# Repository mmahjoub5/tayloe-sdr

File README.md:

# tayloe-sdr
Custom Hardware &amp; SDR with ownership of entire stack

# credits
https://github.com/darius3241/Software-Defined-Radio

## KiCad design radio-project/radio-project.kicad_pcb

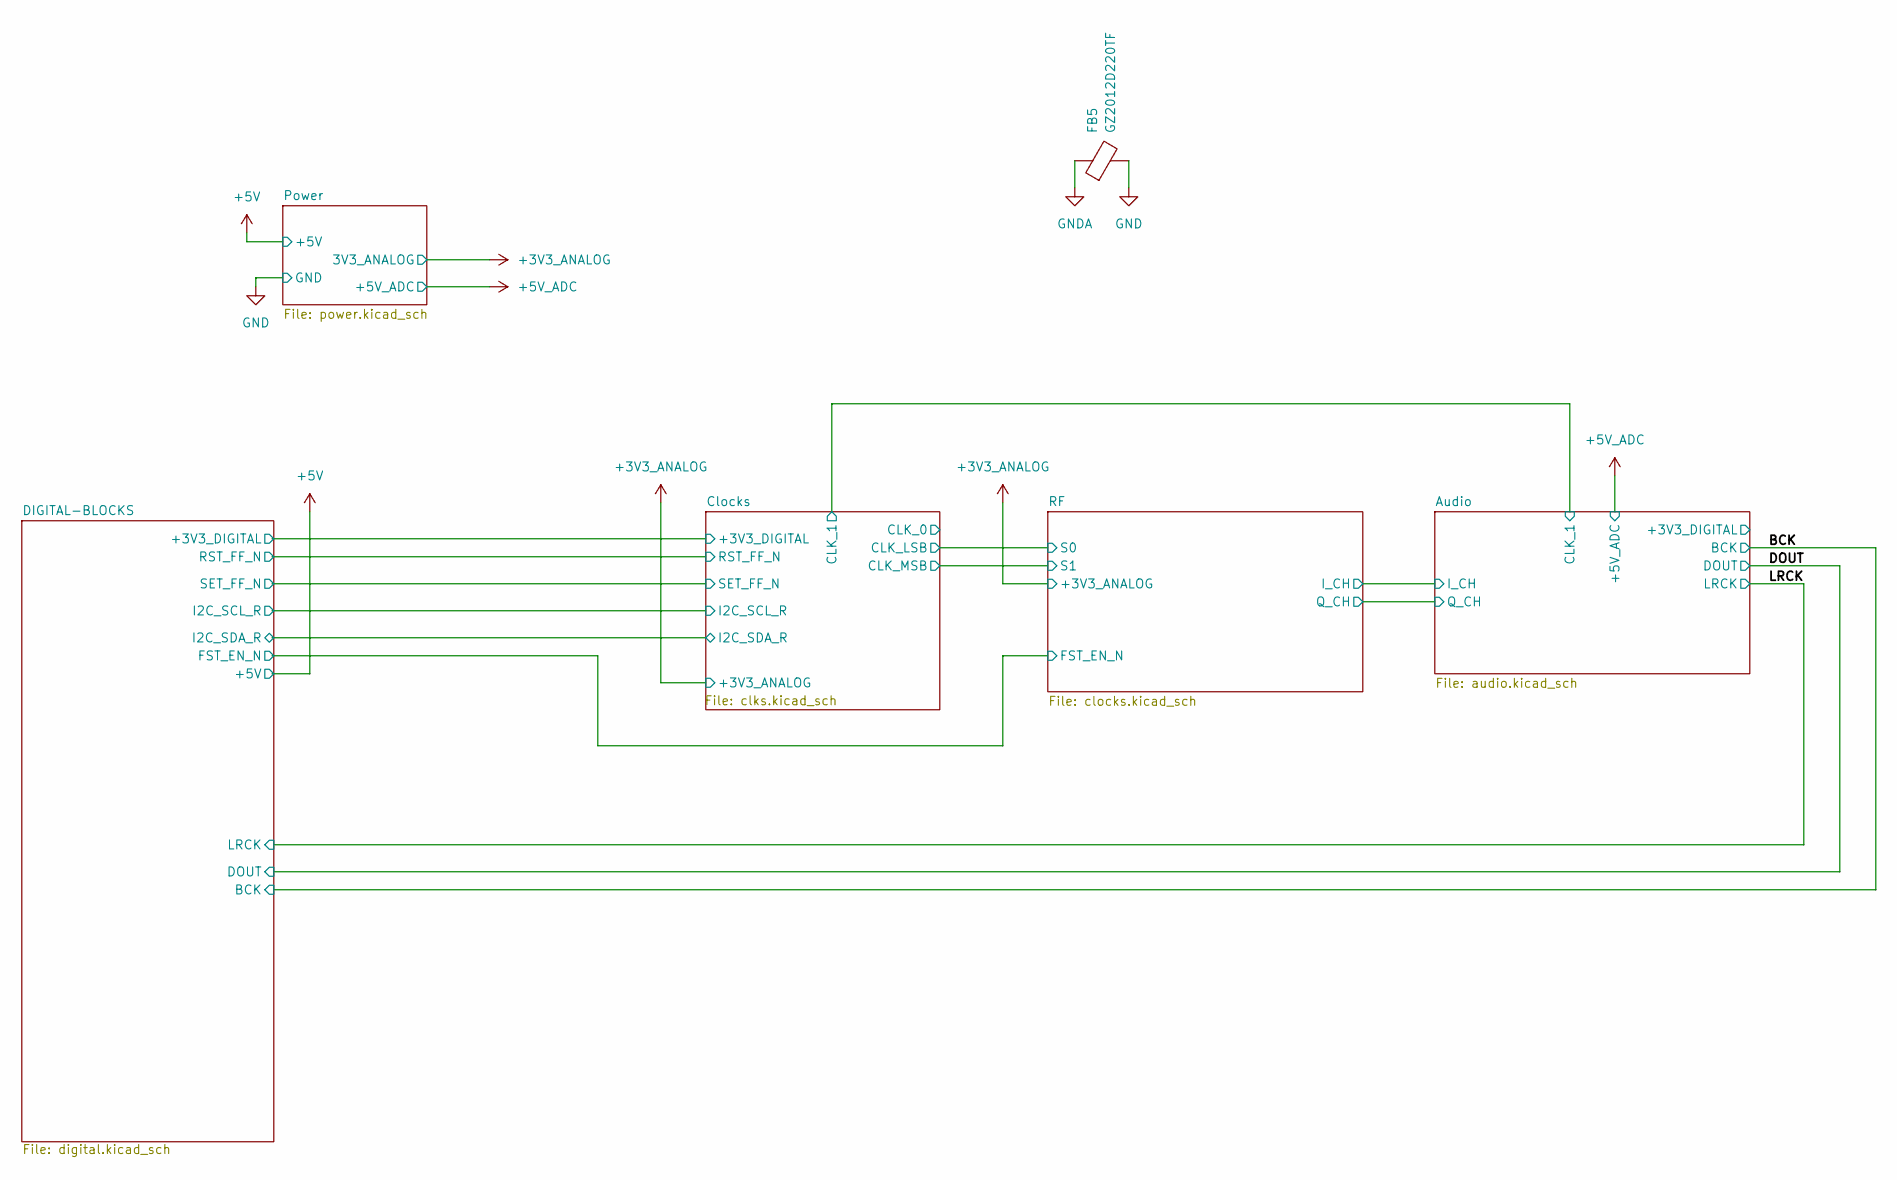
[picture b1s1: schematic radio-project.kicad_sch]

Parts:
FB5: GZ2012D220TF; L_0805_2012Metric

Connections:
GND: FB5.2; also elsewhere on the board
GNDA: FB5.1; also elsewhere on the board

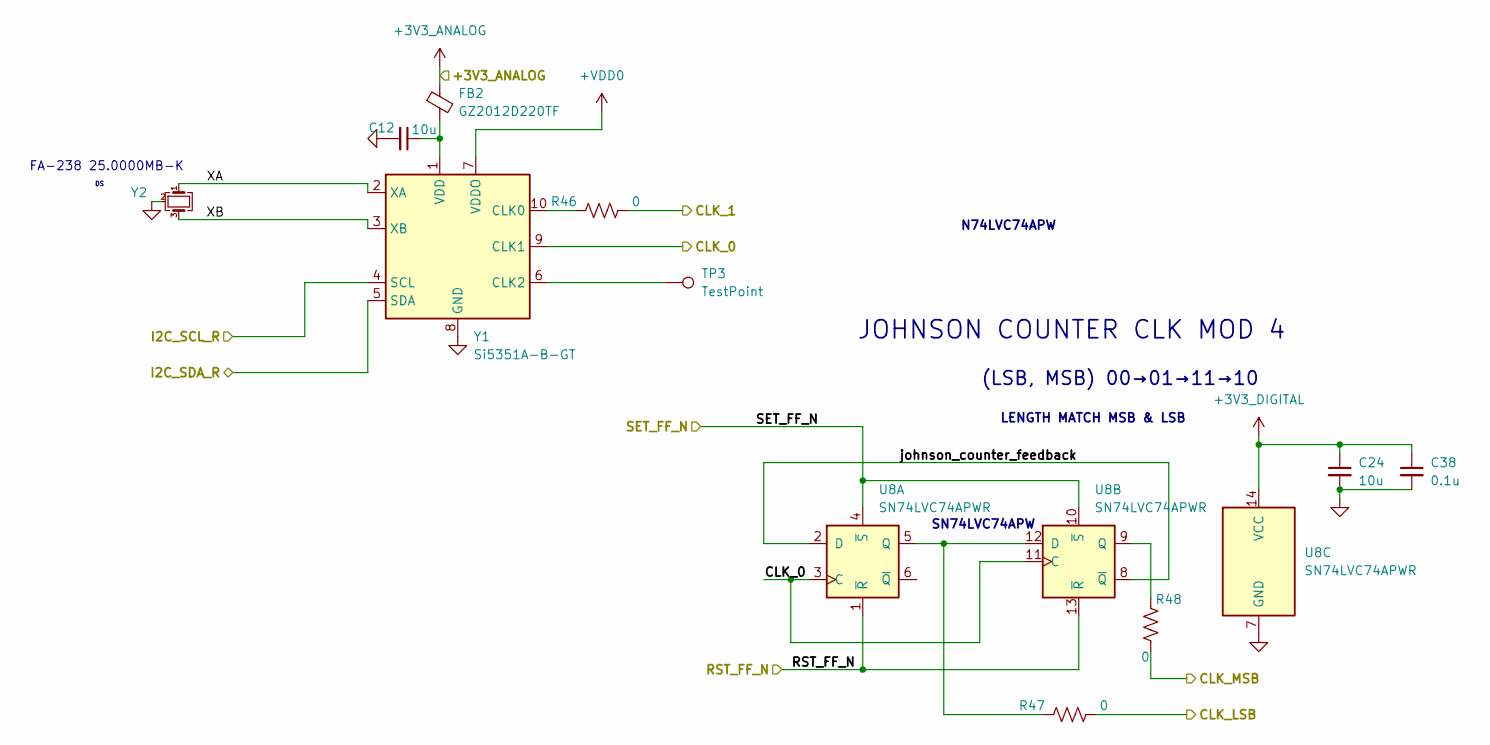
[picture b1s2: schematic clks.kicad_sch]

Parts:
C12, C24: 10u; C_0603_1608Metric
C38: 0.1u; C_0201_0603Metric
FB2: GZ2012D220TF; L_0805_2012Metric
R46, R47, R48: 0; R_0402_1005Metric
TP3: TestPoint; TestPoint_Pad_D1.0mm
U8: SN74LVC74APWR; TSSOP-14_4.4x5mm_P0.65mm
Y1: Si5351A-B-GT; MSOP-10_3x3mm_P0.5mm
Y2: 25Mhz; Crystal_SMD_3225-4Pin_3.2x2.5mm

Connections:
+3V3_ANALOG: FB2.1; also elsewhere on the board
+3V3_DIGITAL: C24.1, C38.1, U8.14 (VCC); also elsewhere on the board
+VDD0: Y1.7 (VDDO)
/Audio/CLK_1: R46.2; also elsewhere on the board
/Clocks/CLK_0: U8.3 (C), U8.11 (C), Y1.9 (CLK1)
/Clocks/CLK_LSB: R47.2; also elsewhere on the board
/Clocks/CLK_MSB: R48.2; also elsewhere on the board
/Clocks/I2C_SCL_R: Y1.4 (SCL); also elsewhere on the board
/Clocks/I2C_SDA_R: Y1.5 (SDA); also elsewhere on the board
/Clocks/RST_FF_N: U8.1 (~R), U8.13 (~R); also elsewhere on the board
/Clocks/SET_FF_N: U8.4 (~S), U8.10 (~S); also elsewhere on the board
/Clocks/XA: Y1.2 (XA), Y2.1
/Clocks/XB: Y1.3 (XB), Y2.3
/Clocks/johnson_counter_feedback: U8.2 (D), U8.8 (~Q)
GND: C12.2, C24.2, C38.2, U8.7 (GND), Y1.8 (GND), Y2.2 (G), Y2.4 (G); also elsewhere on the board
unnamed: R47.1, U8.5 (Q), U8.12 (D)
unnamed: R48.1, U8.9 (Q)
unnamed: R46.1, Y1.10 (CLK0)
unnamed: TP3.1 (1_1), Y1.6 (CLK2)
unnamed: C12.1, FB2.2, Y1.1 (VDD)

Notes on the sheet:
N74LVC74APW
JOHNSON COUNTER CLK MOD 4
FA-238 25.0000MB-K
SN74LVC74APW
(LSB, MSB) 00→01→11→10
LENGTH MATCH MSB & LSB

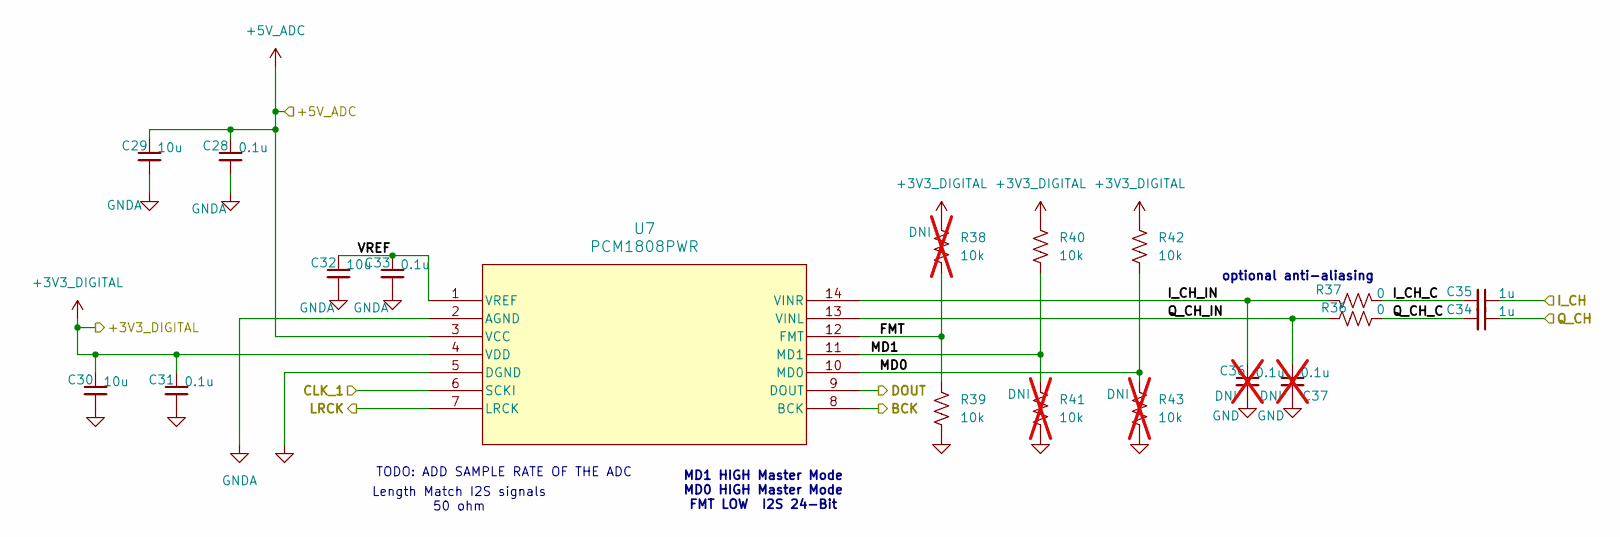
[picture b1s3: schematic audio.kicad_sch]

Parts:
C28, C31: 0.1u; C_0603_1608Metric
C29, C30, C32: 10u; C_0603_1608Metric
C33: 0.1u; C_0402_1005Metric
C34, C35: 1u; C_0402_1005Metric
C36, C37: 0.1u; C_0402_1005Metric; not fitted
R36, R37: 0; R_0402_1005Metric
R38, R41, R43: 10k; R_0402_1005Metric; not fitted
R39, R40, R42: 10k; R_0402_1005Metric
U7: PCM1808PWR; TSSOP-14_4.4x5mm_P0.65mm

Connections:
+3V3_DIGITAL: C30.1, C31.1, R38.1, R40.1, R42.1, U7.4 (VDD); also elsewhere on the board
+5V_ADC: C28.1, C29.1, U7.3 (VCC); also elsewhere on the board
/Audio/CLK_1: U7.6 (SCKI); also elsewhere on the board
/Audio/FMT: R38.2, R39.1, U7.12 (FMT)
/Audio/I_CH: C35.1; also elsewhere on the board
/Audio/I_CH_C: C35.2, R37.2
/Audio/I_CH_IN: C36.1, R37.1, U7.14 (VINR)
/Audio/MD0: R42.2, R43.1, U7.10 (MD0)
/Audio/MD1: R40.2, R41.1, U7.11 (MD1)
/Audio/Q_CH: C34.1; also elsewhere on the board
/Audio/Q_CH_C: C34.2, R36.2
/Audio/Q_CH_IN: C37.1, R36.1, U7.13 (VINL)
/Audio/VREF: C32.1, C33.1, U7.1 (VREF)
/BCK: U7.8 (BCK); also elsewhere on the board
/DOUT: U7.9 (DOUT); also elsewhere on the board
/LRCK: U7.7 (LRCK); also elsewhere on the board
GND: C30.2, C31.2, C36.2, C37.2, R39.2, R41.2, R43.2, U7.5 (DGND); also elsewhere on the board
GNDA: C28.2, C29.2, C32.2, C33.2, U7.2 (AGND); also elsewhere on the board

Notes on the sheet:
MD1 HIGH Master Mode MD0 HIGH Master Mode FMT LOW I2S 24-Bit
optional anti-aliasing
Length Match I2S signals 50 ohm
TODO: ADD SAMPLE RATE OF THE ADC

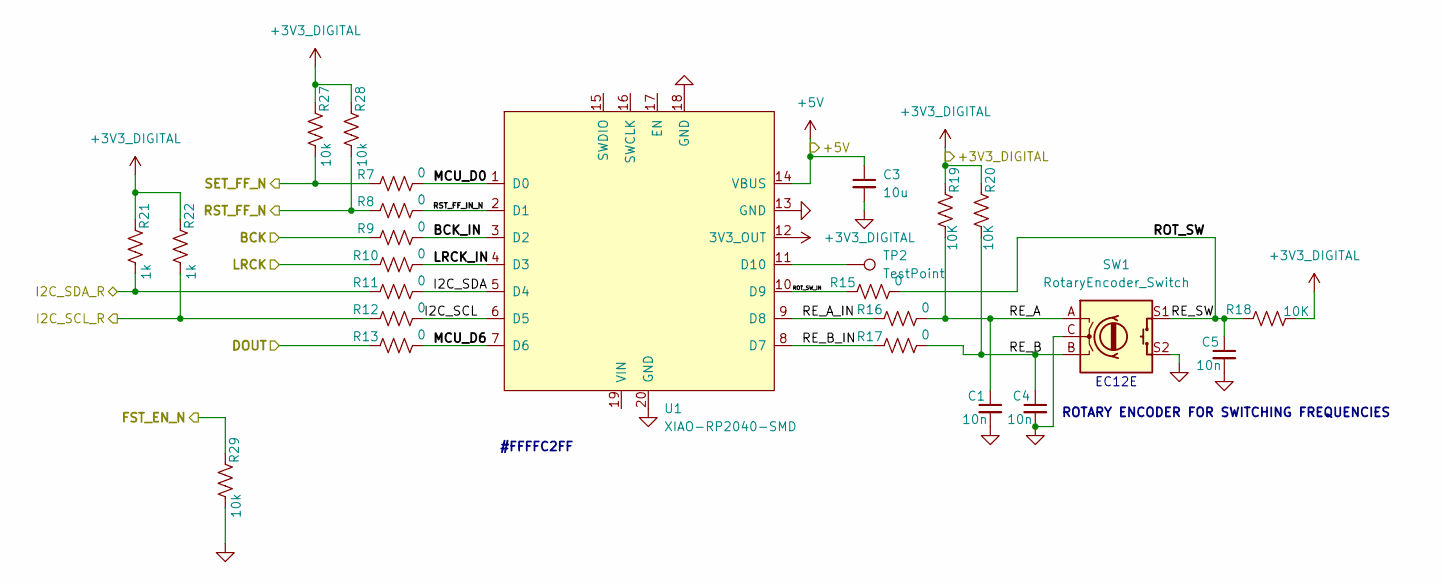
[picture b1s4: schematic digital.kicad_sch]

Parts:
C1, C4, C5: 10n; C_0402_1005Metric
C3: 10u; C_0603_1608Metric
R7, R8, R9, R10, R11, R12, R13, R15, R16, R17: 0; R_0402_1005Metric
R18, R19, R20: 10K; R_0402_1005Metric
R21, R22: 1k; R_0402_1005Metric
R27, R28, R29: 10k; R_0402_1005Metric
SW1: RotaryEncoder_Switch; RotaryEncoder_Alps_EC12E-Switch_Vertical_H20mm
TP2: TestPoint; TestPoint_Pad_D2.0mm
U1: XIAO-RP2040-SMD

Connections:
+3V3_DIGITAL: R18.1, R19.2, R20.2, R21.2, R22.2, R27.2, R28.2, U1.12 (3V3_OUT); also elsewhere on the board
+5V: C3.1, U1.14 (VBUS); also elsewhere on the board
/BCK: R9.2; also elsewhere on the board
/Clocks/I2C_SCL_R: R12.2, R22.1; also elsewhere on the board
/Clocks/I2C_SDA_R: R11.2, R21.1; also elsewhere on the board
/Clocks/RST_FF_N: R8.2, R28.1; also elsewhere on the board
/Clocks/SET_FF_N: R7.2, R27.1; also elsewhere on the board
/DIGITAL-BLOCKS/BCK_IN: R9.1, U1.3 (D2)
/DIGITAL-BLOCKS/I2C_SCL: R12.1, U1.6 (D5)
/DIGITAL-BLOCKS/I2C_SDA: R11.1, U1.5 (D4)
/DIGITAL-BLOCKS/LRCK_IN: R10.1, U1.4 (D3)
/DIGITAL-BLOCKS/MCU_D0: R7.1, U1.1 (D0)
/DIGITAL-BLOCKS/MCU_D6: R13.1, U1.7 (D6)
/DIGITAL-BLOCKS/RE_A: C1.1, R16.1, R19.1, SW1.A
/DIGITAL-BLOCKS/RE_A_IN: R16.2, U1.9 (D8)
/DIGITAL-BLOCKS/RE_B: C4.1, R17.1, R20.1, SW1.B
/DIGITAL-BLOCKS/RE_B_IN: R17.2, U1.8 (D7)
/DIGITAL-BLOCKS/RE_SW: C5.1, R15.1, R18.2, SW1.S1
/DIGITAL-BLOCKS/ROT_SW_IN: R15.2, U1.10 (D9)
/DIGITAL-BLOCKS/RST_FF_IN_N: R8.1, U1.2 (D1)
/DOUT: R13.2; also elsewhere on the board
/LRCK: R10.2; also elsewhere on the board
/RF/FST_EN_N: R29.2; also elsewhere on the board
GND: C1.2, C3.2, C4.2, C5.2, R29.1, SW1.C, SW1.S2, U1.13 (GND), U1.18 (GND), U1.20 (GND); also elsewhere on the board
unnamed: TP2.1 (1_1), U1.11 (D10)

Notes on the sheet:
EC12E
ROTARY ENCODER FOR SWITCHING FREQUENCIES
#FFFFC2FF

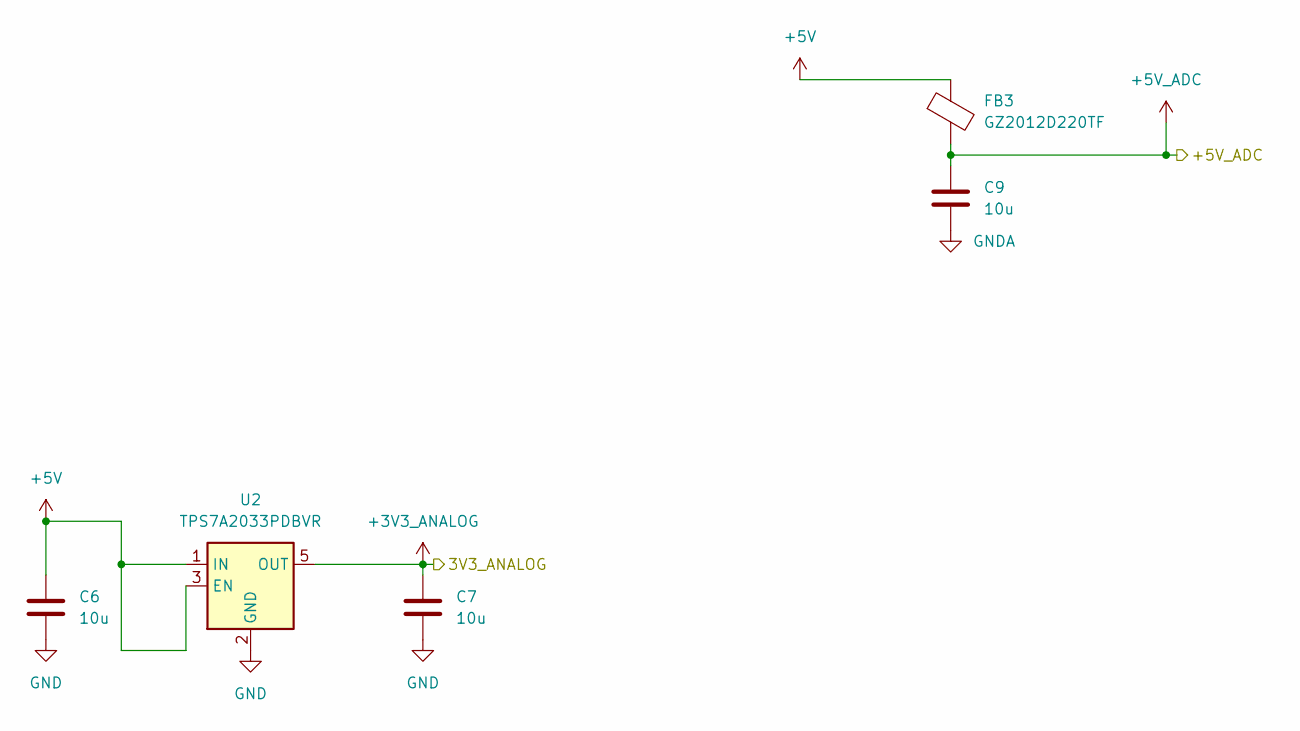
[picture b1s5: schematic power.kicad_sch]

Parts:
C6, C7, C9: 10u; C_0603_1608Metric_Pad1.08x0.95mm_HandSolder
FB3: GZ2012D220TF; L_0805_2012Metric
U2: TPS7A2033PDBVR; SOT-23-5

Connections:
+3V3_ANALOG: C7.1, U2.5 (OUT); also elsewhere on the board
+5V: C6.1, FB3.1, U2.1 (IN), U2.3 (EN); also elsewhere on the board
+5V_ADC: C9.1, FB3.2; also elsewhere on the board
GND: C6.2, C7.2, U2.2 (GND); also elsewhere on the board
GNDA: C9.2; also elsewhere on the board

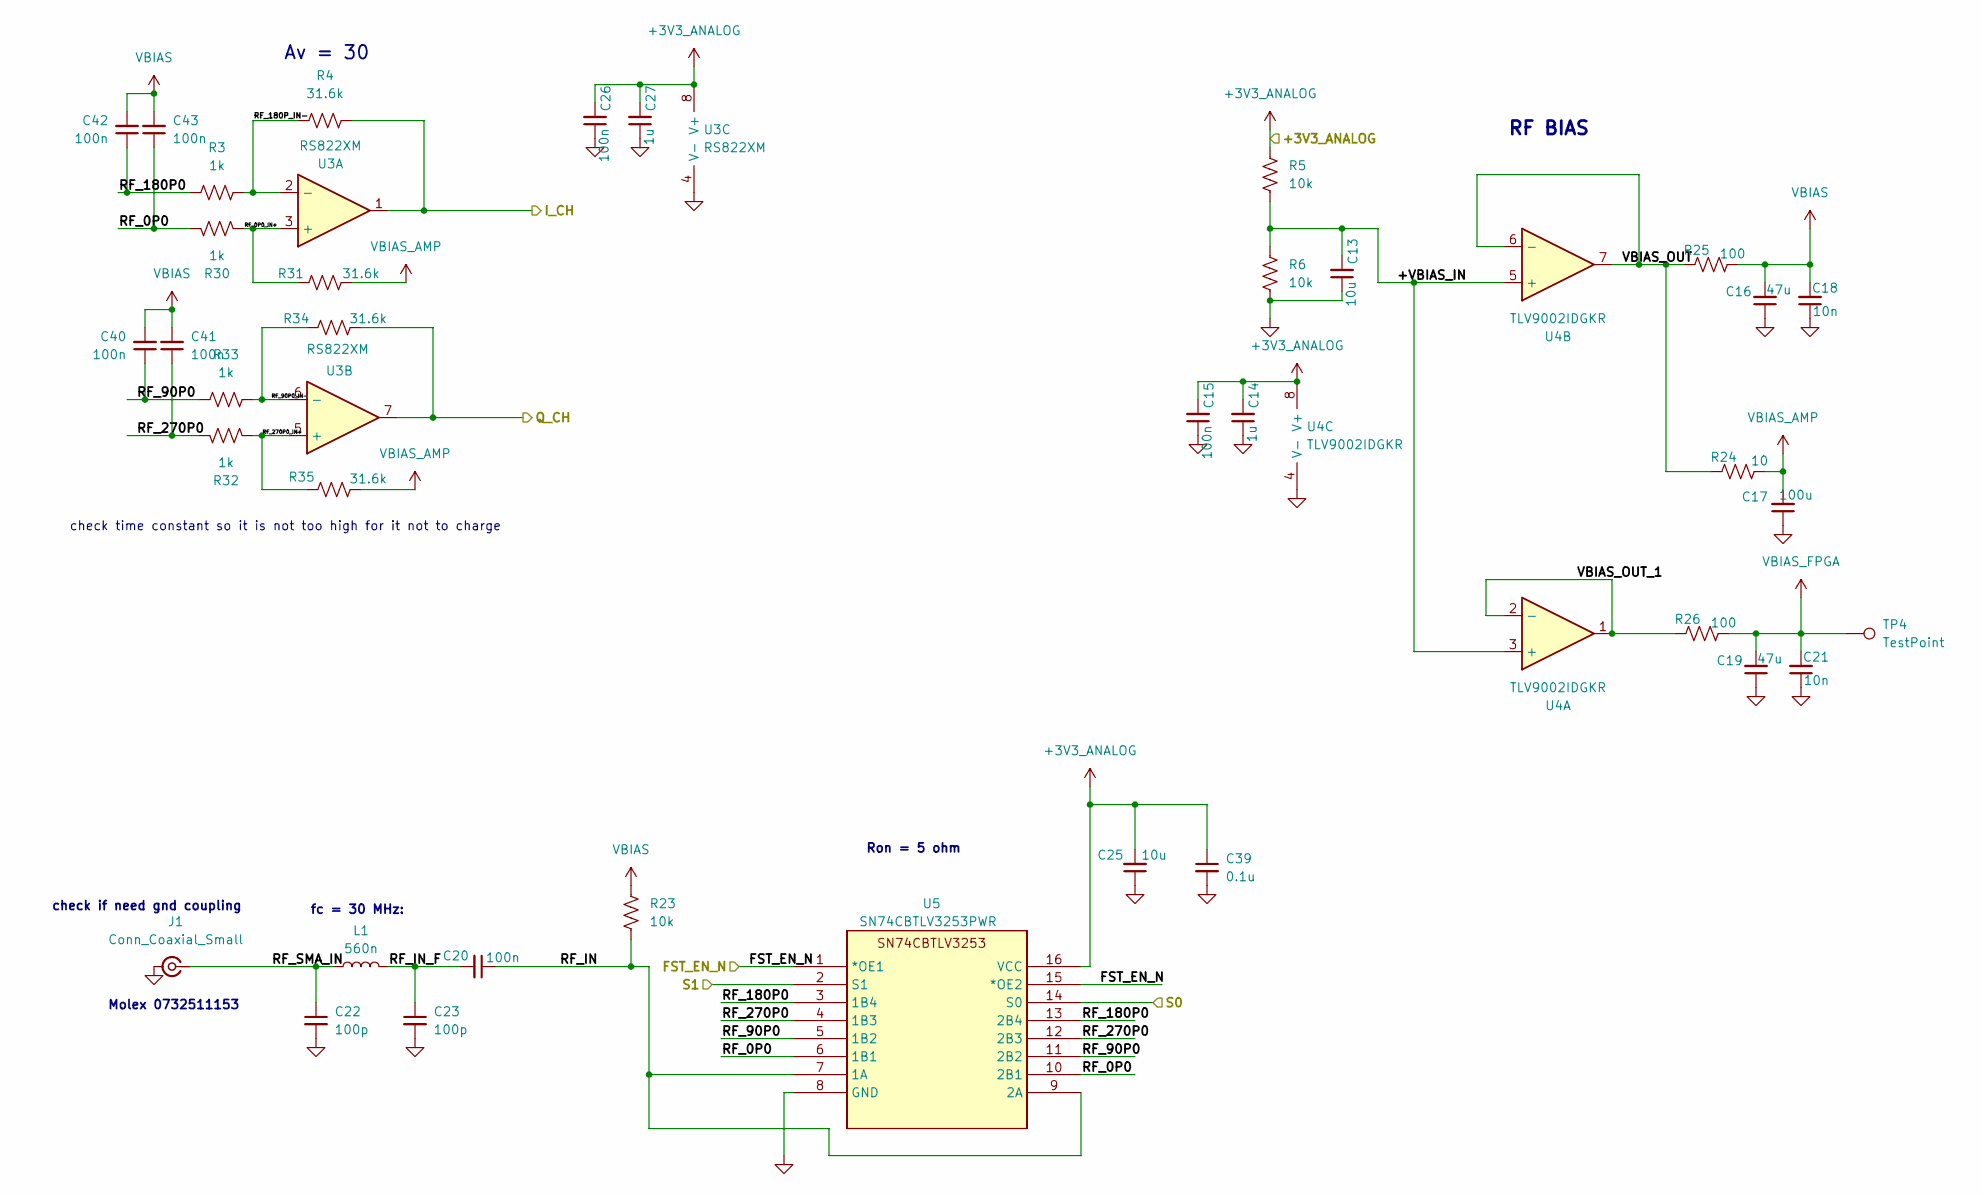
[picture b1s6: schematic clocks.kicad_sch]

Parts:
C13, C25: 10u; C_0603_1608Metric
C14, C27: 1u; C_0603_1608Metric
C15, C20, C26: 100n; C_0402_1005Metric
C16, C19: 47u; C_0805_2012Metric
C17: 100u; C_0805_2012Metric
C18, C21: 10n; C_0402_1005Metric
C22, C23: 100p; C_0402_1005Metric
C39: 0.1u; C_0201_0603Metric
C40, C41, C42, C43: 100n; C_0805_2012Metric
J1: Conn_Coaxial_Small; SMA_Samtec_SMA-J-P-H-ST-EM1_EdgeMount
L1: 560n; L_0603_1608Metric
R3, R30, R32, R33: 1k; R_0402_1005Metric
R4, R31, R34, R35: 31.6k; R_0402_1005Metric
R5, R6, R23: 10k; R_0402_1005Metric
R24: 10; R_0402_1005Metric
R25, R26: 100; R_0402_1005Metric
TP4: TestPoint; TestPoint_Pad_D2.0mm
U3: RS822XM; MSOP-8_3x3mm_P0.65mm
U4: TLV9002IDGKR; MSOP-8_3x3mm_P0.65mm
U5: SN74CBTLV3253PWR

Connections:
+3V3_ANALOG: C14.2, C15.2, C25.2, C26.2, C27.2, C39.1, R5.1, U3.8 (V+), U4.8 (V+), U5.16 (VCC); also elsewhere on the board
/Audio/I_CH: R4.2, U3.1; also elsewhere on the board
/Audio/Q_CH: R34.2, U3.7; also elsewhere on the board
/Clocks/CLK_LSB: U5.14 (S0); also elsewhere on the board
/Clocks/CLK_MSB: U5.2 (S1); also elsewhere on the board
/RF/+VBIAS_IN: C13.2, R5.2, R6.1, U4.3 (+), U4.5 (+)
/RF/FST_EN_N: U5.1 (*OE1), U5.15 (*OE2); also elsewhere on the board
/RF/RF_0P0: C43.1, R30.1, U5.6 (1B1), U5.10 (2B1)
/RF/RF_0P0_IN+: R30.2, R31.1, U3.3 (+)
/RF/RF_90P0: C40.1, R33.1, U5.5 (1B2), U5.11 (2B2)
/RF/RF_90P0_IN-: R33.2, R34.1, U3.6 (-)
/RF/RF_180P0: C42.1, R3.1, U5.3 (1B4), U5.13 (2B4)
/RF/RF_180P_IN-: R3.2, R4.1, U3.2 (-)
/RF/RF_270P0: C41.1, R32.1, U5.4 (1B3), U5.12 (2B3)
/RF/RF_270P0_IN+: R32.2, R35.1, U3.5 (+)
/RF/RF_IN: C20.1, R23.2, U5.7 (1A), U5.9 (2A)
/RF/RF_IN_F: C20.2, C23.1, L1.2
/RF/RF_SMA_IN: C22.1, J1.1 (In), L1.1
/RF/VBIAS_OUT: R24.1, R25.1, U4.6 (-), U4.7
/RF/VBIAS_OUT_1: R26.1, U4.1, U4.2 (-)
GND: C13.1, C14.1, C15.1, C16.1, C17.1, C18.1, C19.1, C21.1, C22.2, C23.2, C25.1, C26.1, C27.1, C39.2, J1.2 (Ext), R6.2, U3.4 (V-), U4.4 (V-), U5.8 (GND); also elsewhere on the board
VBIAS: C16.2, C18.2, C40.2, C41.2, C42.2, C43.2, R23.1, R25.2
VBIAS_AMP: C17.2, R24.2, R31.2, R35.2
VBIAS_FPGA: C19.2, C21.2, R26.2, TP4.1 (1_1)

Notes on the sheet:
Av = 30
check if need gnd coupling
RF BIAS
Molex 0732511153
check time constant so it is not too high for it not to charge
fc = 30 MHz:
Ron = 5 ohm

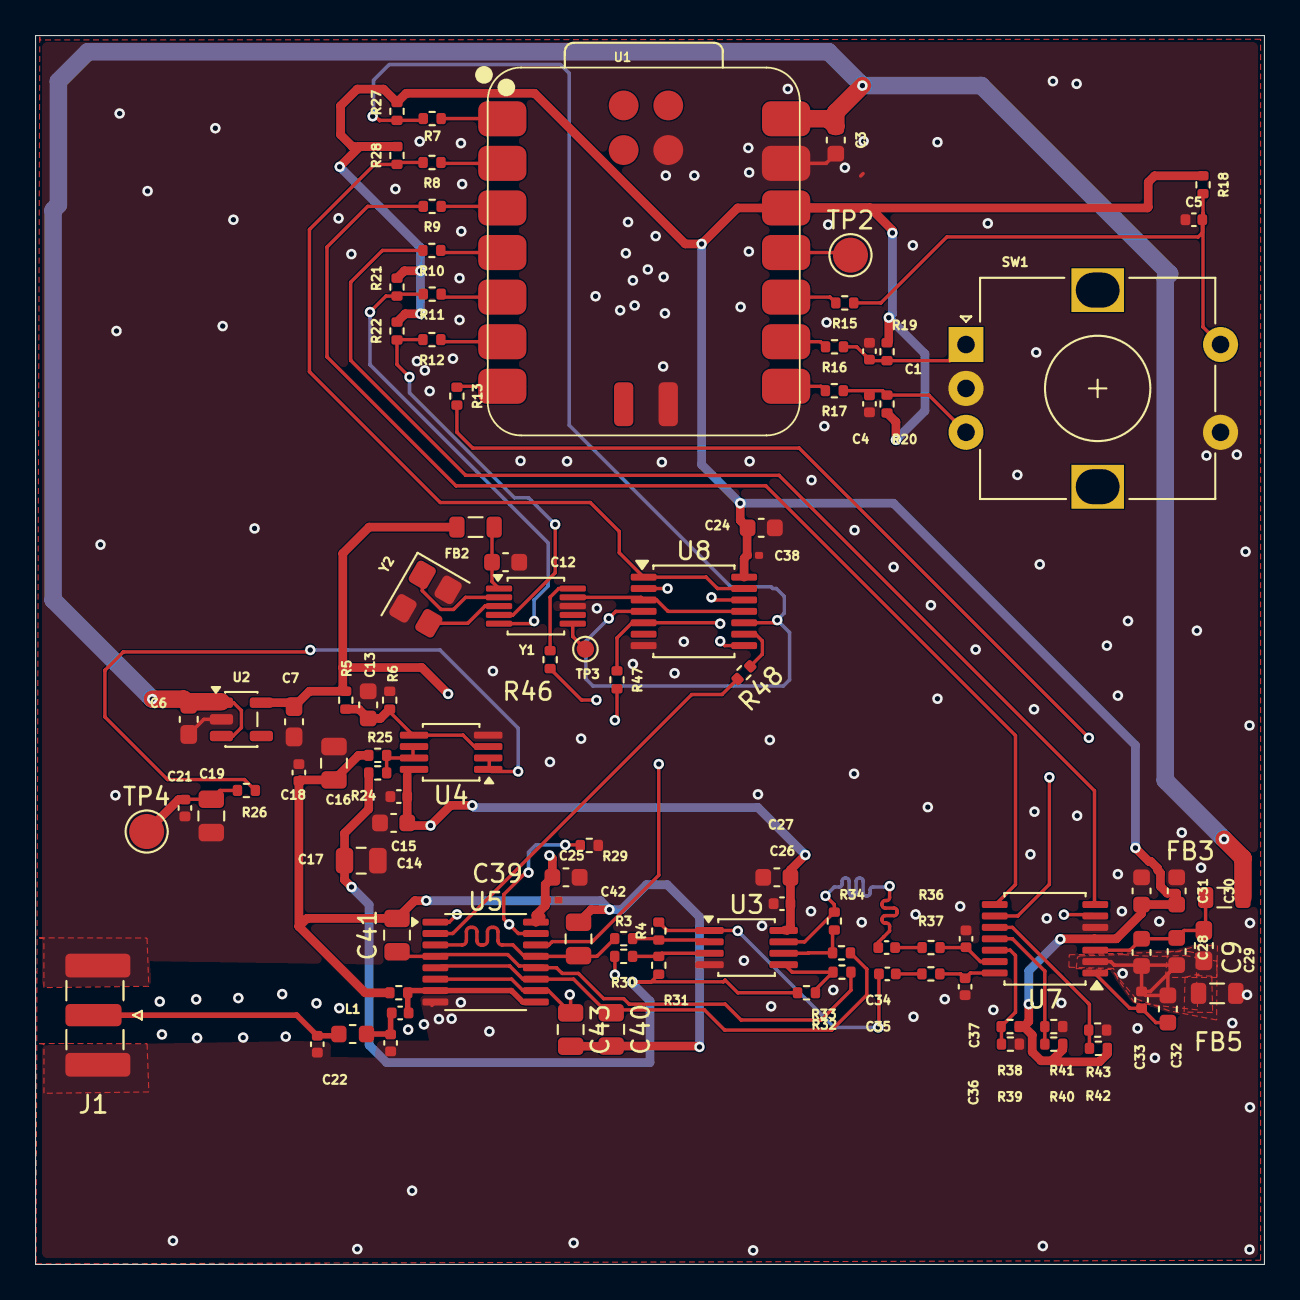
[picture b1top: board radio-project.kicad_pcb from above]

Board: 4 copper layers, 70.0 x 70.0 mm, 100 parts (0 on the bottom side), 67 nets.
